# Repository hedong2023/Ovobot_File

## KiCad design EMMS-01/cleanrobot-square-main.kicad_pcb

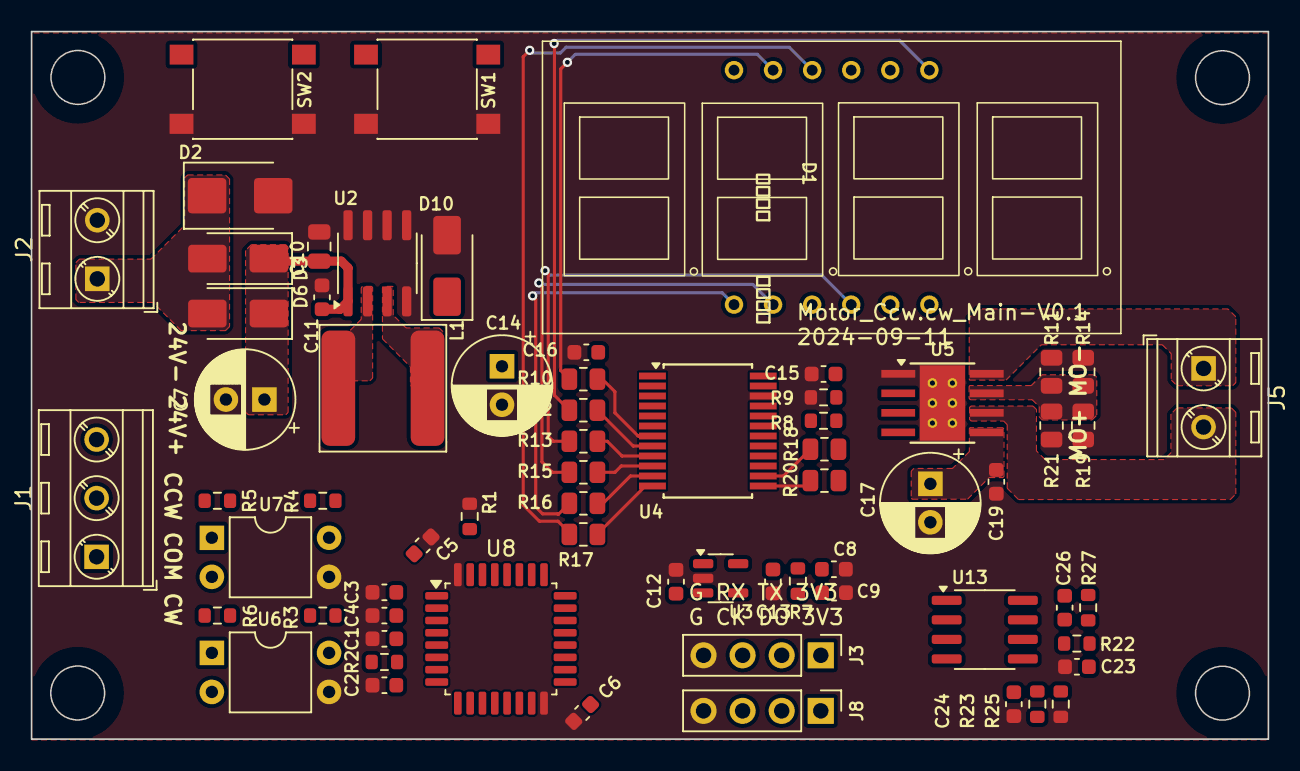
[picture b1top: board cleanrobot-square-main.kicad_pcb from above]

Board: 2 copper layers, 80.4 x 46.0 mm, 67 parts (0 on the bottom side), 54 nets.

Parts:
C1, C2, C3, C4, C5, C15, C16, C19, C23, C24, C26: 0.1uF; C_0603_1608Metric
C6: 4.7uF; C_0603_1608Metric
C7, C17: 100uF/35V; CP_Radial_D6.3mm_P2.50mm
C8, C9, C11, C12, C13: 1uF; C_0603_1608Metric
C10: 10uF/35V; C_0805_2012Metric
C14: 470uF/10V; CP_Radial_D6.3mm_P2.50mm
D1: LED_3x0.56
D2: SMBJ26CA; D_SMB
D3, D6, D10: SS34; D_SMA
J1: KF128-3.81-3P; TerminalBlock_MetzConnect_Type086_RT03403HBLC_1x03_P3.81mm_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
J2, J5: KF128-3.81-2P; TerminalBlock_MetzConnect_Type086_RT03402HBLC_1x02_P3.81mm_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
J3, J8: Conn_01x04; PinHeader_1x04_P2.54mm_Vertical
L1: 68uH; L_GZJ_WNR8045
R1, R3, R4, R5, R6, R23: 10K/1%; R_0603_1608Metric
R2, R7: 0R; R_0603_1608Metric
R8: 6.8K/1%; R_0603_1608Metric
R9: 3.3K/1%; R_0603_1608Metric
R10, R12, R13, R15, R16, R17, R20: 10R; R_0805_2012Metric
R11, R14, R19, R21: 1R/1%; R_0805_2012Metric
R18: 27R; R_0805_2012Metric
R22: 15K/1%; R_0603_1608Metric
R25: 2K/1%; R_0603_1608Metric
R27: 51K/1%; R_0603_1608Metric
SW1, SW2: 6x6x5mm; SW_Push_1P1T_NO_6x6mm_H5.0mm
U2: XL1509-5.0E1; SOIC-8_3.9x4.9mm_P1.27mm
U3: DS8562-33S5; SOT-23-5
U4: SSOP-24_5.3x8.2mm_P0.65mm
U5: OCB8870ESAE; Texas_HTSOP-8-1EP_3.9x4.9mm_P1.27mm_EP2.95x4.9mm_Mask2.4x3.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
U6, U7: TLP785; DIP-4_W7.62mm
U8: STM32F030K6Tx; LQFP-32_7x7mm_P0.8mm
U13: LMV358TP-SR; SOIC-8_3.9x4.9mm_P1.27mm

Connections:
+3.3VA: C9.1, R7.2, R23.1
+3V3: C3.2, C4.2, C5.2, C6.2, C8.1, C13.1, C16.1, J3.1, J8.1, R2.2, R3.1, R4.1, R7.1, R8.1, U3.5 (VOUT), U4.6 (VDD), U8.1 (VDD), U8.5 (VDDA), U8.17 (VDD)
+5V: C12.1, C14.1, L1.2, U2.3 (FB), U3.1 (VIN), U3.3 (EN)
+24V: D2.1 (K), D3.2 (A), D6.2 (A), J2.1
/main/A: D1.11 (A), R10.1
/main/ADC2_MOTOR: C26.2, R27.2, U8.12 (PA6), U13.7
/main/B: D1.7 (B), R12.1
/main/C: D1.4 (C), R13.1
/main/COM1: D1.12 (DIG1), U4.24 (GR1)
/main/COM2: D1.9 (DIG2), U4.23 (GR2)
/main/COM3: D1.8 (DIG3), U4.21 (GR3)
/main/D: D1.2 (D), R15.1
/main/DP: D1.3 (DP), R18.2
/main/E: D1.1 (E), R16.1
/main/F: D1.10 (F), R17.1
/main/G: D1.5 (G), R20.2
/main/KEY_CCW: R4.2, U7.4, U8.15 (PB1)
/main/KEY_CW: R3.2, U6.4, U8.14 (PB0)
/main/MOTOR_KEY_CCW: J1.3, R5.1
/main/MOTOR_KEY_CW: J1.1, R6.1
/main/PWM_RIGHT1: U5.3 (IN1), U8.20 (PA10)
/main/PWM_RIGHT2: U5.2 (IN2), U8.21 (PA11)
/main/R_MOTOR_OUT+: J5.2, U5.6 (OUT1)
/main/R_MOTOR_OUT-: J5.1, U5.8 (OUT2)
/main/SPI1_CLK: U4.2 (CLK), U8.26 (PB3)
/main/SPI1_DIN: U4.1 (DIO), U8.28 (PB5)
/main/SPI1_STB: U4.3 (STB), U8.27 (PB4)
/main/SWCLK: J8.3, U8.24 (PA14)
/main/SWDIO: J8.2, U8.23 (PA13)
/main/SW_PWM+: SW2.1, U8.18 (PA8)
/main/SW_PWM-: SW1.1, U8.19 (PA9)
/main/UART1_RX: J3.3, U8.30 (PB7)
/main/UART1_TX: J3.2, U8.29 (PB6)
/main/VERF_1.078V: C15.1, R8.2, R9.1, U5.4 (VREF)
/main/VREF55: C24.1, R23.2, R25.1, U13.5 (+)
GND: C1.1, C2.1, C3.1, C4.1, C5.1, C6.1, C7.2, C8.2, C9.2, C10.2, C11.2, C12.2, C13.2, C14.2, C15.2, C16.2, C17.2, C19.2, C23.2, C24.2, D2.2 (A), D10.2 (A), J2.2, J3.4, J8.4, R1.1, R9.2, R11.2, R14.2, R19.2, R21.2, R25.2, SW1.2, SW2.2, U2.4 (EN), U2.5 (GND), U2.6 (GND), U2.7 (GND), U2.8 (GND), U3.2 (GND), U4.22 (GND), U5.1 (GND), U5.9 (GND), U6.3, U7.3, U8.16 (VSS), U8.32 (VSS)
GND1: J1.2, U6.2, U7.2
unnamed: C2.2, R2.1
unnamed: D10.1 (K), L1.1, U2.2 (OUT)
unnamed: R5.2, U7.1
unnamed: R6.2, U6.1
unnamed: R10.2, U4.7 (SEG1/KSI)
unnamed: R12.2, U4.8 (SEG2/KS2)
unnamed: R13.2, U4.9 (SEG3/KS3)
unnamed: R15.2, U4.10 (SEG4/KS4)
unnamed: R16.2, U4.11 (SEG5/KS5)
unnamed: R17.2, U4.12 (SEG6/KS6)
unnamed: R20.1, U4.13 (SEG7)
unnamed: R18.1, U4.14 (SEG8)
unnamed: C23.1, R11.1, R14.1, R19.1, R21.1, R22.1, U5.7 (ISEN)
unnamed: R1.2, U8.31 (BOOT0)
unnamed: C1.2, U8.4 (NRST)
unnamed: C26.1, R22.2, R27.1, U13.6 (-)
VDD: C7.1, C10.1, C11.1, C17.1, C19.1, D3.1 (K), D6.1 (K), U2.1 (VIN), U5.5 (VM)

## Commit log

2024-09-30 上传全部工程文件
2024-09-30 修改电机PWM工程文件
